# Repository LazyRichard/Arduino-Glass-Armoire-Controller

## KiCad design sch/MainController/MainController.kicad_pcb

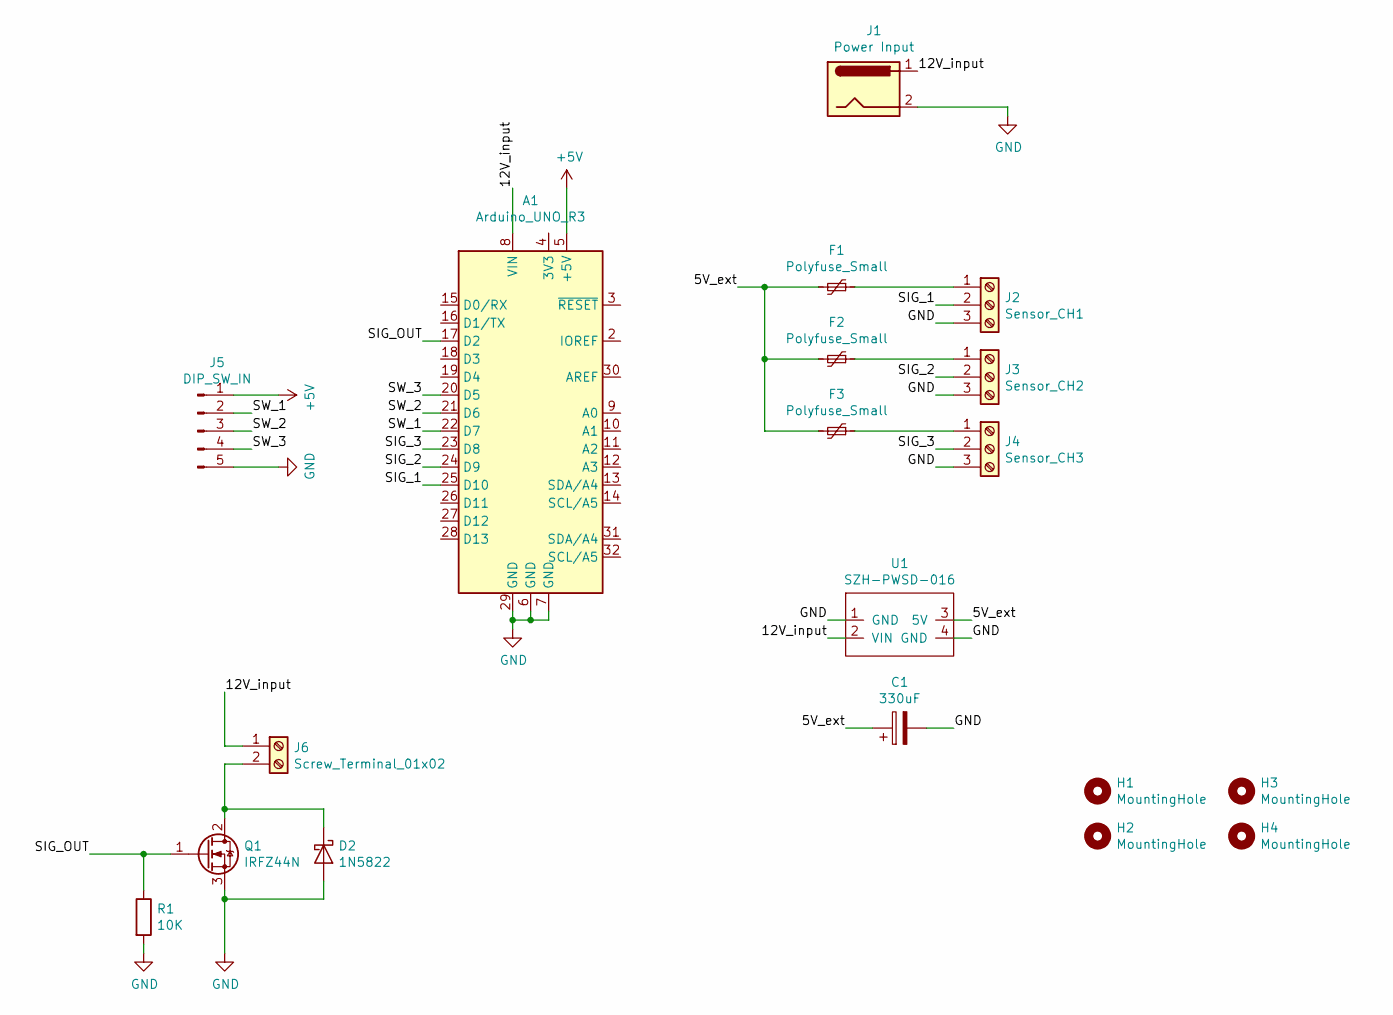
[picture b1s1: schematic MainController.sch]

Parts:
A1: Arduino_UNO_R3
C1: 330uF; CP_Radial_D8.0mm_P3.80mm
D2: 1N5822; D_DO-201AD_P5.08mm_Vertical_KathodeUp
F1, F2, F3: Polyfuse_Small; Fuse_1812_4532Metric_Pad1.30x3.40mm_HandSolder
H1, H2, H3, H4: MountingHole; MountingHole_3mm
J1: Power Input; PJ-002B
J2: Sensor_CH1; ECH381R-3p
J3: Sensor_CH2; ECH381R-3p
J4: Sensor_CH3; ECH381R-3p
J5: DIP_SW_IN; PinHeader_1x05_P2.54mm_Vertical
J6: Screw_Terminal_01x02; ECH381V-2p
Q1: IRFZ44N; TO-220-3_Vertical
R1: 10K; R_1806_4516Metric_Pad1.57x1.80mm_HandSolder
U1: SZH-PWSD-016

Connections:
+5V: A1.5 (+5V), J5.1
/5V_ext: C1.1, F1.2, F2.2, F3.2, U1.3 (5V)
/12V_input: A1.8 (VIN), J1.1, J6.1, U1.2 (VIN)
/SIG_1: A1.25 (D10), J2.2
/SIG_2: A1.24 (D9), J3.2
/SIG_3: A1.23 (D8), J4.2
/SIG_OUT: A1.17 (D2), Q1.1 (G), R1.1
/SW_1: A1.22 (D7), J5.2
/SW_2: A1.21 (D6), J5.3
/SW_3: A1.20 (D5), J5.4
GND: A1.6 (GND), A1.7 (GND), A1.29 (GND), C1.2, D2.2 (A), J1.2, J2.3, J3.3, J4.3, J5.5, Q1.3 (S), R1.2, U1.1 (GND), U1.4 (GND)
unnamed: D2.1 (K), J6.2, Q1.2 (D)
unnamed: F1.1, J2.1
unnamed: F2.1, J3.1
unnamed: F3.1, J4.1

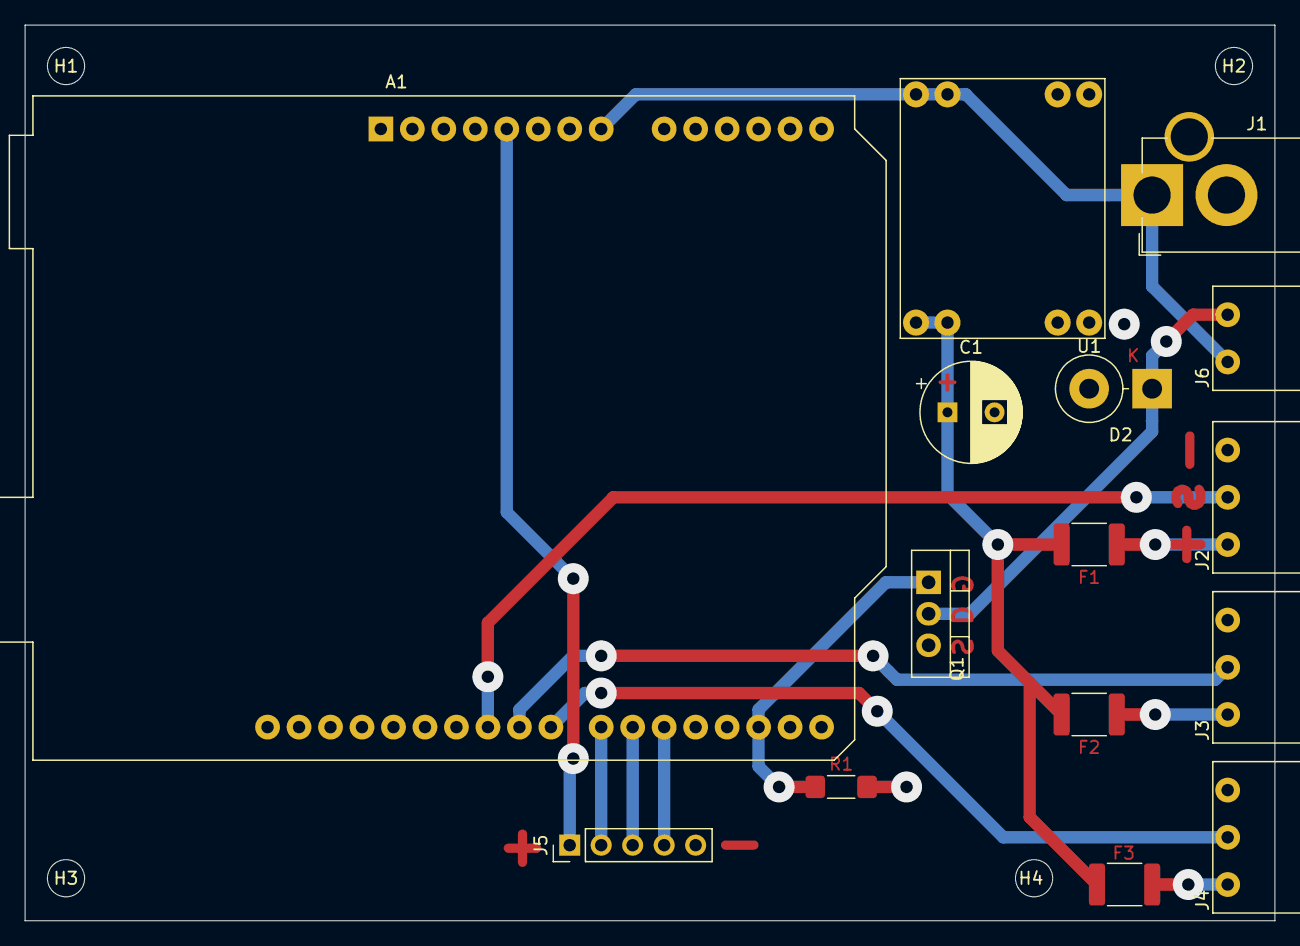
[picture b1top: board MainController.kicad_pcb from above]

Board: 2 copper layers, 100.8 x 72.3 mm, 19 parts (0 on the bottom side), 15 nets.

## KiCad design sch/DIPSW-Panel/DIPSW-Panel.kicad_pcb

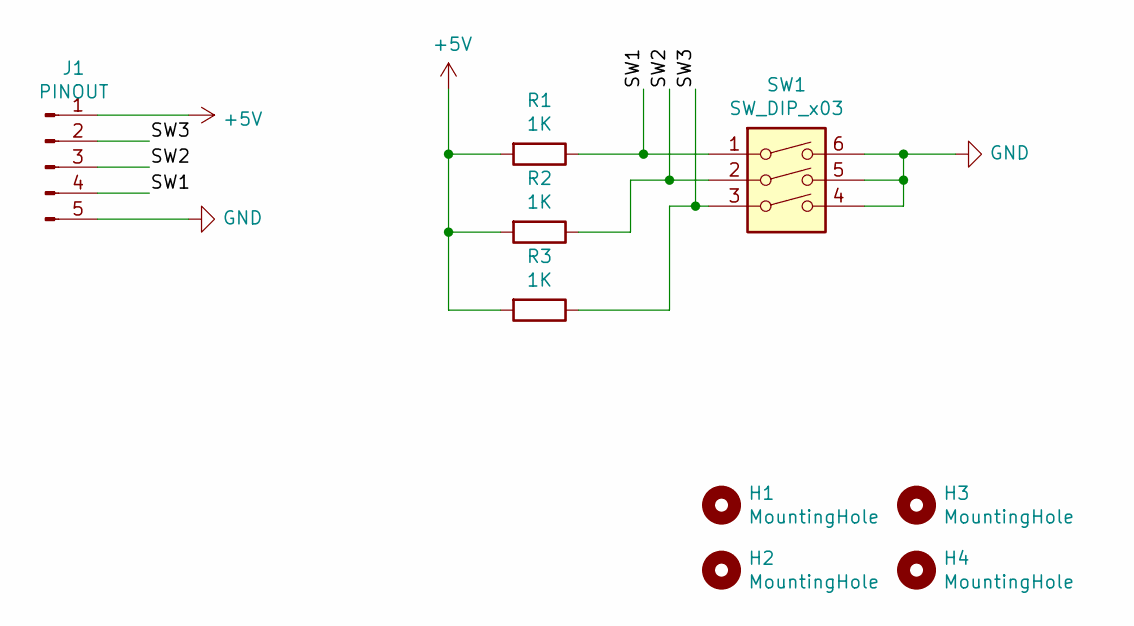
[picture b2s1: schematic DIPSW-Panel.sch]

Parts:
H1, H2, H3, H4: MountingHole; MountingHole_2mm
J1: PINOUT; PinHeader_1x05_P2.54mm_Vertical
R1, R2, R3: 1K; R_0603_1608Metric_Pad1.05x0.95mm_HandSolder
SW1: SW_DIP_x03; DIP-6_W7.62mm_LongPads

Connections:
+5V: J1.1, R1.2, R2.2, R3.2
/SW1: J1.4, R1.1, SW1.1
/SW2: J1.3, R2.1, SW1.2
/SW3: J1.2, R3.1, SW1.3
GND: J1.5, SW1.4, SW1.5, SW1.6

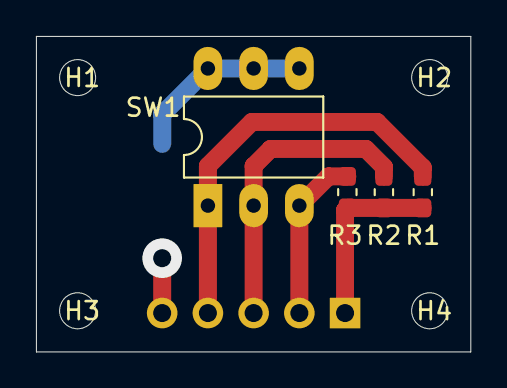
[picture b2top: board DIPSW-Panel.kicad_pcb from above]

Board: 2 copper layers, 24.1 x 17.5 mm, 9 parts (1 on the bottom side), 5 nets.

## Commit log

2020-01-13 add pcb
2020-01-16 [PCB] housekeeping
2020-01-17 remove zip file
2020-01-17 add test firm
2020-01-17 add basic firmware
2020-01-17 [pcb] update pcb pattern
2020-01-30 [pcb] fix tr control circuit and update pcb layout
